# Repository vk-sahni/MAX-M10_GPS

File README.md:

# MAX-M10S GNSS Receiver Board

A KiCad hardware design for a compact GNSS receiver based on the u-blox MAX-M10S module. The circular board brings out UART and I2C host interfaces, an SMA RF connector for an external GNSS antenna, a backup-cell footprint, and a PPS timing signal.

> **Design status:** this is a development design, not a production-released module. The current KiCad checks report open electrical/manufacturing items; see [Production readiness](#production-readiness) before building or ordering boards.

## Board views

### Front / component side

### Back side

### 3D renders from the STEP model

Rendered from [`MAX-M10_GPS.step`](MAX-M10_GPS.step) (colored mechanical model).

| Top | Isometric front |
|-----|-----------------|
|  |  |

| Isometric back | Bottom |
|----------------|--------|
|  |  |

### Close-ups

| MAX-M10S GNSS module (U1) and RF section | Edge-mount SMA antenna connector (J1) |
|---|---|
|  |  |

| I2C header (J2), jumper (JP1) and power LED | UART header (J3) and board overview |
|---|---|
|  |  |

| Backup cell (BT2), PPS LED and signal resistors | Side profile (component heights) |
|---|---|
|  |  |

The annotations identify board features and connectors. Connector pin numbering below follows the schematic/netlist; confirm pin 1 against the PCB silkscreen before wiring.

## Design overview

| Feature | Design detail |
| --- | --- |
| GNSS receiver | u-blox MAX-M10S (`U1`) |
| Board outline | Circular, approximately 36 mm diameter |
| PCB stackup | 4 copper layers; 1.6 mm nominal total thickness |
| RF connector | Edge-mount SMA (`J1`); antenna is external and not included |
| Host interfaces | 4-pin JST-SH I2C (`J2`) and UART (`J3`) |
| Backup supply | Seiko ML414H rechargeable backup cell (`BT2`) |
| Timing output | PPS signal brought to a board pad/test point |
| Design source | KiCad schematic and PCB in this repository |

The design's supply net is marked **+3.3 V**. The MAX-M10S device itself has a 1.65–3.6 V supply range; this does not make the whole board tolerant of arbitrary input voltages. Supply the board with a regulated 3.3 V on the connector's 3V3 pin. There is no USB interface.

## Connector pinouts

### `J2` — I2C and 3.3 V power

| Pin | Signal | Description |
| ---: | --- | --- |
| 1 | +3.3 V | Board supply |
| 2 | SDA | I2C data |
| 3 | SCL | I2C clock |
| 4 | GND | Ground |

### `J3` — UART and 3.3 V power

| Pin | Signal | Description |
| ---: | --- | --- |
| 1 | +3.3 V | Board supply |
| 2 | TXD | Receiver transmit; connect to host RX |
| 3 | RXD | Receiver input; connect to host TX |
| 4 | GND | Ground |

Both connectors expose the same board supply and ground. Do not connect multiple supplies at once unless the system power design explicitly permits it. Check the connector orientation and pin 1 on the physical PCB before applying power.

## RF antenna

`J1` is the board-edge SMA RF connection for an external GNSS antenna. The antenna is not integrated into the board. Use an antenna compatible with the MAX-M10S RF input and the intended installation; place it with a clear view of the sky and follow the antenna manufacturer's feed/bias requirements. Do not assume that antenna power is enabled or that any antenna will be supported without checking the schematic and RF path.

## Setup and use

1. Open `MAX-M10_GPS.kicad_pro` with KiCad 10 or a compatible newer release.
2. Review the schematic, PCB, custom SMA footprint library table, and the production-readiness items below.
3. Connect a regulated 3.3 V supply, ground, the host interface, and a suitable external GNSS antenna.
4. If using I2C, configure the solder jumper `JP1` as marked on the PCB to enable the I2C bus pull-up connection.
5. Connect a host to the UART or I2C interface and configure the receiver using the u-blox documentation.
6. Confirm GNSS reception, PPS behavior, power draw, RF performance, and recovery behavior on assembled hardware.

`BT2` is specified as a rechargeable ML414H backup cell. Use only a compatible rechargeable cell and verify the charging/backup circuit before assembly; do not substitute a primary, non-rechargeable coin cell.

## Repository contents

- `MAX-M10_GPS.kicad_pro` — KiCad project
- `MAX-M10_GPS.kicad_sch` — schematic
- `MAX-M10_GPS.kicad_pcb` — PCB layout
- `SMA_Amphenol_132289_EdgeMount_EDITED.pretty/` — project-local SMA footprint
- `fp-lib-table` — project-local footprint library registration
- `Front_MAX-M10_GPS.png`, `Back_MAX-M10_GPS.png` — original 3D board views
- `MAX-M10_GPS_front_annotated.png`, `MAX-M10_GPS_back_annotated.png` — labeled 3D board views
- `MAX-M10_GPS_front_annotated.svg`, `MAX-M10_GPS_back_annotated.svg` — editable annotation overlays
- `manufacturing/gerbers/` — Gerber (RS-274X) layers, Excellon drill files and job file
- `manufacturing/MAX-M10_GPS_BOM.csv`, `manufacturing/MAX-M10_GPS_positions.csv` — BOM and pick-and-place data
- `manufacturing/MAX-M10_GPS.step` — 3D STEP model
- `manufacturing/README.md` — fabrication and assembly notes
- `MAX-M10_GPS.step` — colored 3D STEP model (root copy)
- `docs/renders/` — 3D renders generated from the STEP model
- `docs/MAX-M10_GPS_schematic.pdf` — schematic PDF
- `CHANGELOG.md` — release history

No license file is included: all rights are reserved by the author.

## Production readiness

The current design files were checked with KiCad 10.0.6. These are design-file checks only, not board fabrication, assembly, environmental, or RF qualification:

- **PCB DRC:** 1 violation — solder-mask apertures bridge different nets at the `BT2` backup-cell footprint, between the footprint polygon and pad 1 (`BACKUP`). Resolve this with the footprint/mask design and confirm the fabrication interpretation before release.
- **Unconnected PCB pads:** 0 reported.
- **Schematic ERC:** 3 errors for power-input pins without a recognized power-output driver, and 15 warnings. Review whether the power flags and repeated local/global labels are intentional, then clear or explicitly document each result.
- **BOM completeness:** resistor `R11` is marked `TBD`; finalize its value/part and review the complete BOM and assembly notes.

Before production, resolve or formally disposition the reported DRC/ERC findings; finalize and verify the BOM; review footprints, connector orientation, clearances, and fabrication outputs; and validate the assembled board's supply behavior, GNSS/RF performance, antenna configuration, UART/I2C/PPS operation, and environmental requirements. No production, accuracy, or certification claim is made by this repository.

## References

- [u-blox MAX-M10S data sheet](https://content.u-blox.com/sites/default/files/MAX-M10S_DataSheet_UBX-20035208.pdf)
- [u-blox documentation portal](https://www.u-blox.com/en/product/max-m10-series)

## GitHub repository description

> Circular u-blox MAX-M10S GNSS receiver breakout with SMA antenna input, UART, I2C, backup-cell support, and KiCad design files.

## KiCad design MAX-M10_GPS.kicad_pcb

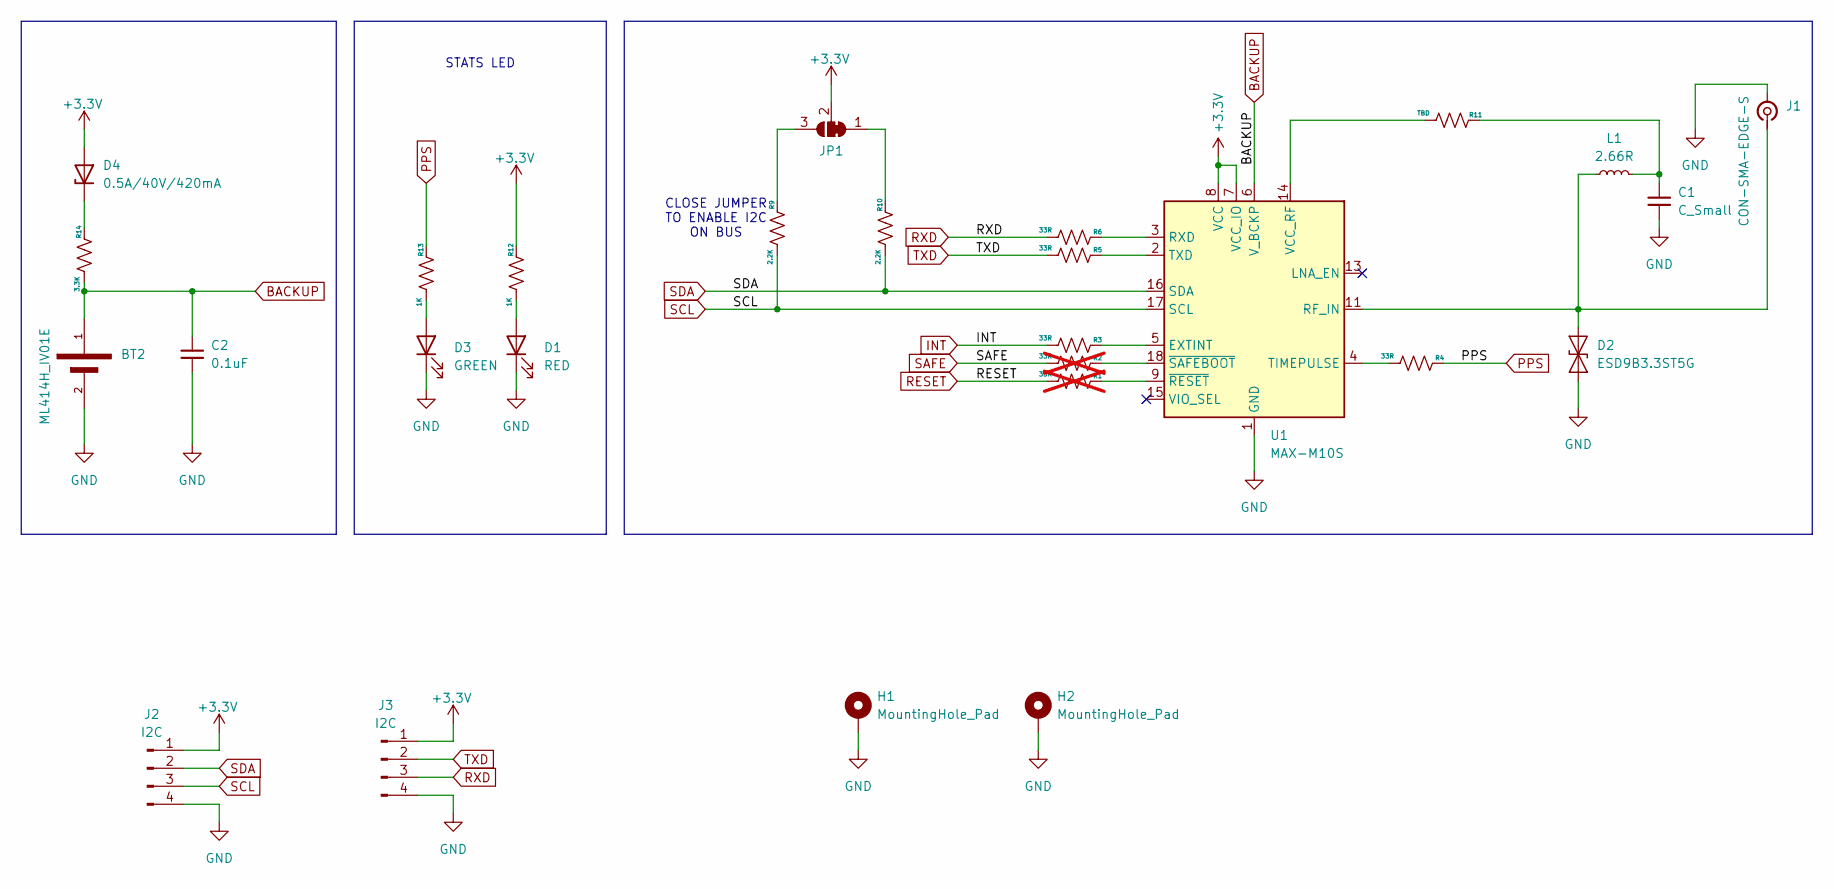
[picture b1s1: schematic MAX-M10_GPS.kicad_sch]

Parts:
BT2: ML414H_IV01E; SEIKO_ML414H_IV01E; DigiKey_Part_Number 728-1052-1-ND
C1: C_Small; C_0603_1608Metric
C2: 0.1uF; C_0603_1608Metric
D1: RED; LED_0603_1608Metric
D2: ESD9B3.3ST5G; D_SOD-923
D3: GREEN; LED_0603_1608Metric
D4: 0.5A/40V/420mA; D_0603_1608Metric
H1, H2: MountingHole_Pad; MountingHole_2.2mm_M2_Pad_Via
J1: CON-SMA-EDGE-S; SMA_Amphenol_132289_EdgeMount
J2, J3: I2C; JST_SH_SM04B-SRSS-TB_1x04-1MP_P1.00mm_Horizontal
JP1: CLOSE JUMPER TO ENABLE I2C ON BUS; SolderJumper-3_P1.3mm_Bridged12_RoundedPad1.0x1.5mm
L1: 2.66R; L_0603_1608Metric
R1, R2: 33R; R_0603_1608Metric; not fitted
R3, R4, R5, R6: 33R; R_0603_1608Metric
R9, R10: 2.2K; R_0603_1608Metric
R11: TBD; R_0603_1608Metric
R12, R13: 1K; R_0603_1608Metric
R14: 3.3K; R_0603_1608Metric
U1: MAX-M10S; ublox_MAX

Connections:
+3.3V: D4.2 (A), J2.1, J3.1, JP1.2 (C), R12.2, U1.7 (VCC_IO), U1.8 (VCC)
BACKUP: BT2.1, C2.1, R14.1, U1.6 (V_BCKP)
GND: BT2.2, C1.2, C2.2, D1.1 (K), D2.1 (A1), D3.1 (K), H1.1 (1_1), H2.1 (1_1), J1.2 (Ext), J2.4, J3.4, U1.1 (GND), U1.10 (GND), U1.12 (GND)
INT: R3.1
unnamed: C1.1, L1.2, R11.2
unnamed: D1.2 (A), R12.1
unnamed: D2.2 (A2), J1.1 (In), L1.1, U1.11 (RF_IN)
unnamed: D3.2 (A), R13.1
unnamed: D4.1 (K), R14.2
unnamed: JP1.1 (A), R10.2
unnamed: JP1.3 (B), R9.2
unnamed: R3.2, U1.5 (EXTINT)
unnamed: R6.2, U1.3 (RXD)
unnamed: R4.1, U1.4 (TIMEPULSE)
unnamed: R5.2, U1.2 (TXD)
unnamed: R11.1, U1.14 (VCC_RF)
unnamed: R1.2, U1.9 (~RESET)
unnamed: R2.2, U1.18 (~SAFEBOOT)
PPS: R4.2, R13.2
RXD: J3.3, R6.1
SCL: J2.3, R9.1, U1.17 (SCL)
SDA: J2.2, R10.1, U1.16 (SDA)
TXD: J3.2, R5.1

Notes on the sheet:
STATS LED
CLOSE JUMPER TO ENABLE I2C ON BUS

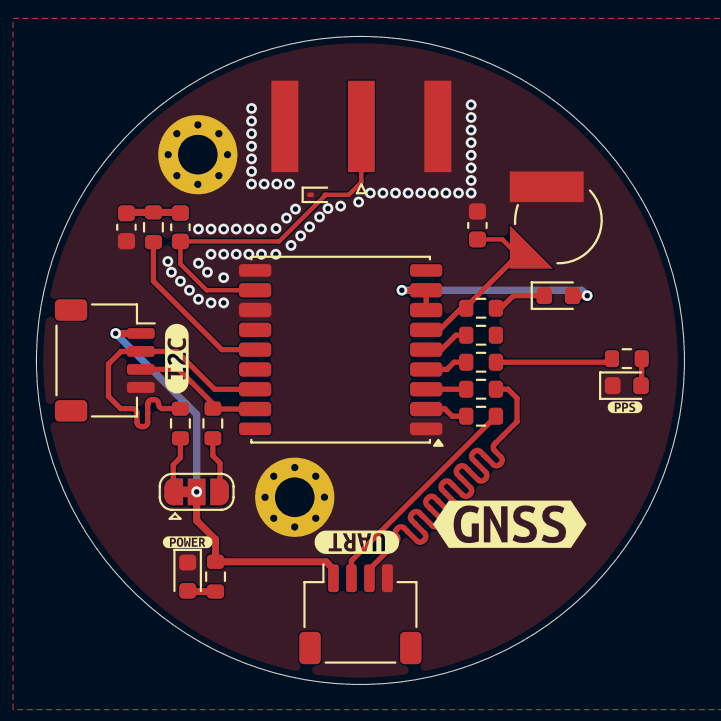
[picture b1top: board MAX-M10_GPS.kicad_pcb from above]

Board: 4 copper layers, 36.0 x 36.0 mm, 31 parts (1 on the bottom side), 20 nets.

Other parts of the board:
kibuzzard-6ACAB4B2: G***; kibuzzard-6ACAB4B2
kibuzzard-6ACAB6CD: G***; kibuzzard-6ACAB6CD
kibuzzard-6ACAB6E4: G***; kibuzzard-6ACAB6E4
kibuzzard-6ACAB40A: G***; kibuzzard-6ACAB40A
kibuzzard-6ACAB677: G***; kibuzzard-6ACAB677
kibuzzard-6ACAB690: G***; kibuzzard-6ACAB690

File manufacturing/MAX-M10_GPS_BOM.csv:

"Reference","Value","Footprint","QUANTITY","MP","MF","DigiKey_Part_Number"
"BT2","ML414H_IV01E","ML414H_IV01E:SEIKO_ML414H_IV01E","1","ML414H IV01E","Seiko Instruments","728-1052-1-ND"
"C1","C_Small","Capacitor_SMD:C_0603_1608Metric","1","","",""
"C2","0.1uF","Capacitor_SMD:C_0603_1608Metric","1","","",""
"D1","RED","LED_SMD:LED_0603_1608Metric","1","","",""
"D2","ESD9B3.3ST5G","Diode_SMD:D_SOD-923","1","","",""
"D3","GREEN","LED_SMD:LED_0603_1608Metric","1","","",""
"D4","0.5A/40V/420mA","Diode_SMD:D_0603_1608Metric","1","","",""
"J1","CON-SMA-EDGE-S","SMA_Amphenol_132289_EdgeMount_EDITED:SMA_Amphenol_132289_EdgeMount","1","","",""
"J2,J3","I2C","Connector_JST:JST_SH_SM04B-SRSS-TB_1x04-1MP_P1.00mm_Horizontal","2","","",""
"L1","2.66R","Inductor_SMD:L_0603_1608Metric","1","","",""
"R3-R6","33R","Resistor_SMD:R_0603_1608Metric","4","","",""
"R9,R10","2.2K","Resistor_SMD:R_0603_1608Metric","2","","",""
"R11","TBD","Resistor_SMD:R_0603_1608Metric","1","","",""
"R12,R13","1K","Resistor_SMD:R_0603_1608Metric","2","","",""
"R14","3.3K","Resistor_SMD:R_0603_1608Metric","1","","",""
"U1","MAX-M10S","RF_GPS:ublox_MAX","1","","",""
